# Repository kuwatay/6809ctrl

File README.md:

# 6809ctrl (UNDER DEVELOPMENT)
AVR-based supervisor for a 6809E microcomputer based on z80ctrl https://github.com/jblang/z80ctrl

* Arduino Shield style hardware (6809Ectrl-mega)
* Flexible MIT-licensed firmware inhelited from z80ctrl

# Documentation

## Application

## Hardware note
https://github.com/kuwatay/6809ctrl/tree/main/hardware
## Supervisor sample session

## DMA handling

## MIT license
Permission is hereby granted, free of charge, to any person obtaining a copy of this software and associated documentation files (the "Software"), to deal in the Software without restriction, including without limitation the rights to use, copy, modify, merge, publish, distribute, sublicense, and/or sell copies of the Software, and to permit persons to whom the Software is furnished to do so, subject to the following conditions:

The above copyright notice and this permission notice shall be included in all copies or substantial portions of the Software.

THE SOFTWARE IS PROVIDED "AS IS", WITHOUT WARRANTY OF ANY KIND, EXPRESS OR IMPLIED, INCLUDING BUT NOT LIMITED TO THE WARRANTIES OF MERCHANTABILITY, FITNESS FOR A PARTICULAR PURPOSE AND NONINFRINGEMENT. IN NO EVENT SHALL THE AUTHORS OR COPYRIGHT HOLDERS BE LIABLE FOR ANY CLAIM, DAMAGES OR OTHER LIABILITY, WHETHER IN AN ACTION OF CONTRACT, TORT OR OTHERWISE, ARISING FROM, OUT OF OR IN CONNECTION WITH THE SOFTWARE OR THE USE OR OTHER DEALINGS IN THE SOFTWARE.

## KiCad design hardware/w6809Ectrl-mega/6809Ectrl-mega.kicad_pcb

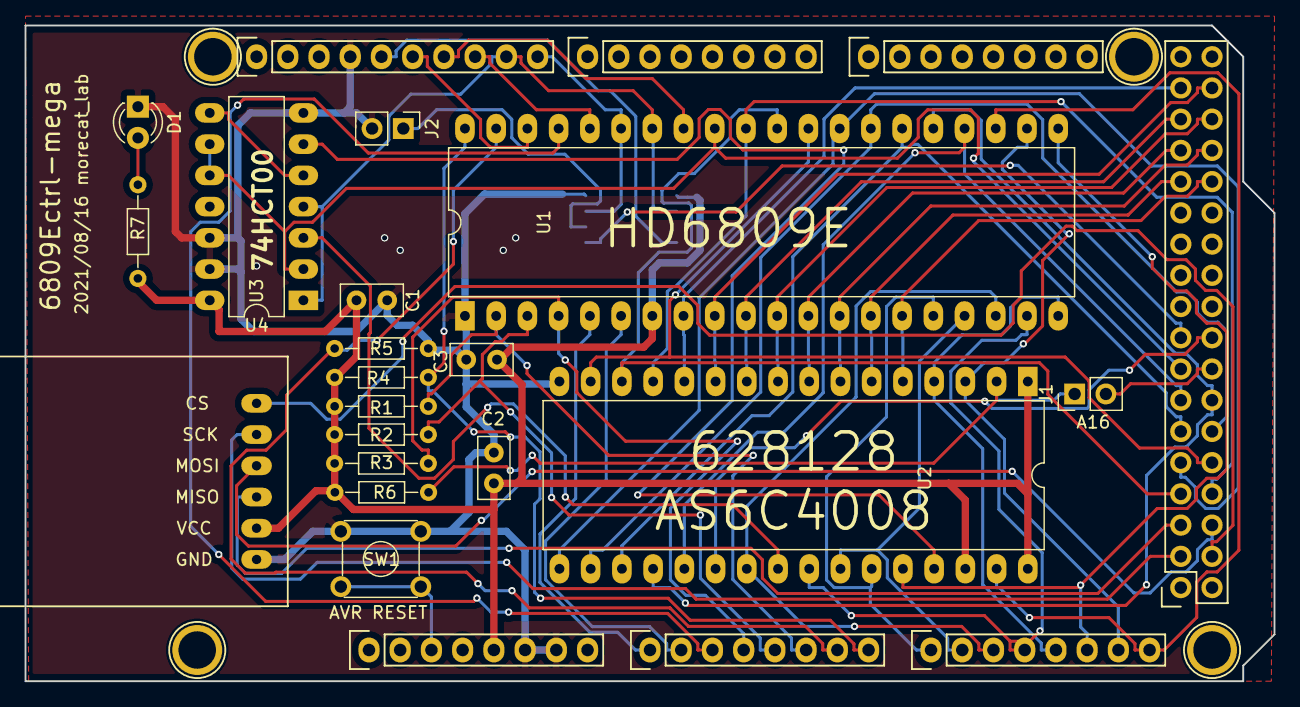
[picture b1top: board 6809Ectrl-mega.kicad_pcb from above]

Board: 2 copper layers, 101.6 x 53.3 mm, 30 parts (1 on the bottom side), 55 nets.

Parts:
C1, C2, C3: 100nF; C_Disc_D5.0mm_W2.5mm_P2.50mm
D1: LED; LED_D3.0mm
J1, J2: Conn_01x02_Female; Pin_Header_Straight_1x02_Pitch2.54mm
P1: Digital; Socket_Strip_Arduino_2x18
P2: Power; Socket_Strip_Arduino_1x08
P3, P4: Analog; Socket_Strip_Arduino_1x08
P5: PWM; Socket_Strip_Arduino_1x10
P6: PWM; Socket_Strip_Arduino_1x08
P7: Communication; Socket_Strip_Arduino_1x08
P8, P10, P11, P13: CONN_01X01; Arduino_1pin
R1, R2, R3, R4, R5, R6: 10k; R_Axial_DIN0204_L3.6mm_D1.6mm_P7.62mm_Horizontal
R7: 1k; R_Axial_DIN0204_L3.6mm_D1.6mm_P7.62mm_Horizontal
SW1: SW_MEC_5E; SW_TH_Tactile_Omron_B3F-10xx
T202: ATtiny202-SS; SO-8_5.3x6.2mm_Pitch1.27mm
U1: MC6809E; DIP-40_W15.24mm_LongPads
U2: AS6C4008; DIP-32_W15.24mm_LongPads
U3: 74HC00; DIP-14_W7.62mm_LongPads
U4: MicroCardAdapter; MicroSDCardAdapter

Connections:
+5V: C1.1, C2.1, C3.1, P2.5, R1.1, R2.1, R3.1, R4.1, R6.2, R7.1, T202.1, U1.7, U2.1, U2.30, U2.32, U3.14, U4.5
A0: P1.33, U1.8, U2.12
A1: P1.34, U1.9, U2.11
A2: P1.31, U1.10, U2.10
A3: P1.32, U1.11, U2.9
A4: P1.29, U1.12, U2.8
A5: P1.30, U1.13, U2.7
A6: P1.27, U1.14, U2.6
A7: P1.28, U1.15, U2.5
A8: P4.1, U1.16, U2.27
A9: P4.2, U1.17, U2.26
A10: P4.3, U1.18, U2.23
A11: P4.4, U1.19, U2.25
A12: P4.5, U1.20, U2.4
A13: P4.6, U1.21, U2.28
A14: P4.7, U1.22, U2.3
A15: P4.8, U1.23, U2.31
A16: J1.2, P1.16
AVMA: P5.8, U1.36
AVR_RESET: P2.3, SW1.3, SW1.4
BA: P3.2, U1.6
BS: P3.1, U1.5
BUSY: P5.7, U1.33
CLK_ENABLE: P5.5, T202.4
CLK_SEL: P1.17, T202.5
D0: P1.8, U1.31, U2.13
D1: P1.7, U1.30, U2.14
D2: P1.10, U1.29, U2.15
D3: P1.9, U1.28, U2.17
D4: P1.12, U1.27, U2.18
D5: P1.11, U1.26, U2.19
D6: P1.14, U1.25, U2.20
D7: P1.13, U1.24, U2.21
E: P5.9, T202.2, U1.34, U3.1, U3.4
FIRQ: P3.4, R3.2, U1.4
GND: C1.2, C2.2, C3.2, D1.1, J2.2, P2.6, P2.7, P5.4, R5.1, SW1.1, SW1.2, T202.8, U1.1, U2.16, U3.7, U3.12, U3.13, U4.6
HALT: P3.8, R4.2, U1.40
IRQ: P3.5, R2.2, U1.3
LIC: P5.6, U1.38
MISO: P1.5, U4.4
MOSI: P1.6, U4.3
NMI: P3.6, R1.2, U1.2
unnamed: D1.2, R7.2
unnamed: J1.1, R6.1, U2.2
unnamed: J2.1, T202.6
unnamed: U2.24, U3.3
unnamed: U2.29, U3.6
unnamed: U3.5, U3.8
Q: P5.10, T202.7, U1.35
RAME: P1.18, U2.22
RESET: P3.3, U1.37
RW: P1.15, U1.32, U3.2, U3.9, U3.10
SCK: P1.3, U4.2
SS: P1.4, U4.1
TSC: P3.7, R5.2, U1.39

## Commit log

2021-08-16 initial commitment
    upload only hardware design.
2021-08-18 upload 6809E clock generator
2021-08-29 add picture of clock generator
